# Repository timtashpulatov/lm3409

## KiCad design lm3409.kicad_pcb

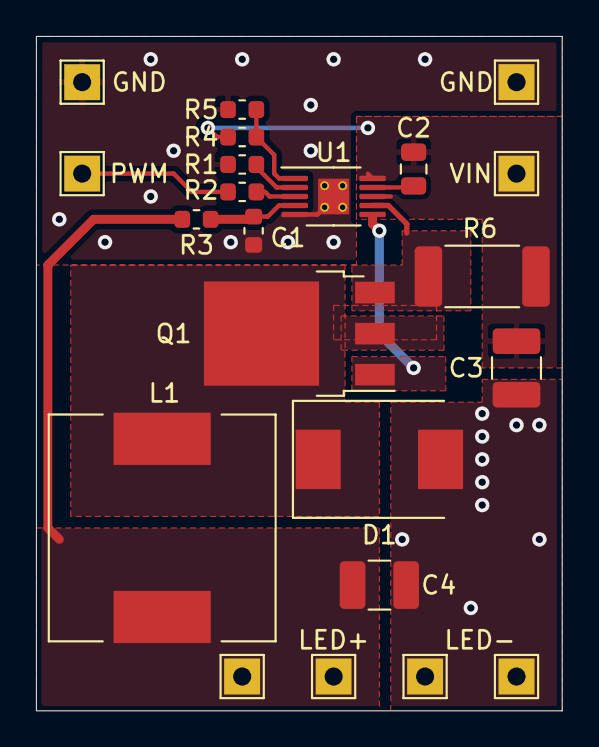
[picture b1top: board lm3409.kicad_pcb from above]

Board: 2 copper layers, 29.2 x 37.5 mm, 22 parts (0 on the bottom side), 12 nets.

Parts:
C1: 470p; C_0603_1608Metric
C2: 1u 50V; C_0805_2012Metric
C3: 10u 50V; C_1210_3225Metric_Pad1.42x2.65mm_HandSolder
C4: TBD; C_1210_3225Metric_Pad1.42x2.65mm_HandSolder
D1: B560C-13-F; D_SMC
GND: GND; TestPoint_THTPad_2.0x2.0mm_Drill1.0mm
GND#2: GND; TestPoint_THTPad_2.0x2.0mm_Drill1.0mm
L1: CDRH127/LDNP-220MC; L_12x12mm_H4.5mm
LED+: +LED; TestPoint_THTPad_2.0x2.0mm_Drill1.0mm
LED+#2: +LED; TestPoint_THTPad_2.0x2.0mm_Drill1.0mm
LED-: LED-; TestPoint_THTPad_2.0x2.0mm_Drill1.0mm
PWM: PWM; TestPoint_THTPad_2.0x2.0mm_Drill1.0mm
Q1: NTD20P06LT4G; TO-252-3_TabPin4
R1: 1K; R_0603_1608Metric
R2: 178K; R_0603_1608Metric
R3: TBD; R_0603_1608Metric
R4: 6K98; R_0603_1608Metric
R5: 49K9; R_0603_1608Metric
R6: WSL2512R2000FEA; R_2512_6332Metric_Pad1.52x3.35mm_HandSolder
TP4: LED-; TestPoint_THTPad_2.0x2.0mm_Drill1.0mm
U1: LM3409HV; MSOP-10-1EP_3x3mm_P0.5mm_EP1.73x1.98mm_ThermalVias
VIN: +VIN; TestPoint_THTPad_2.0x2.0mm_Drill1.0mm

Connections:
/COFF: C1.1, R3.1, U1.4
/CSN: Q1.3, R6.2, U1.7
/IADJ: R2.1, U1.2
/LED+: C4.1, L1.2, LED+.1, LED+#2.1, R3.2
/PGATE: Q1.1, U1.6
/PWM: PWM.1, R1.1
/SW: D1.1, L1.1, Q1.2, Q1.4
/VCC: C2.2, U1.9
/VIN: C2.1, C3.1, R5.1, R6.1, U1.8, U1.10, VIN.1
GND: C1.2, C3.2, C4.2, D1.2, GND.1, GND#2.1, LED-.1, R2.2, R4.2, TP4.1, U1.5, U1.11
unnamed: R1.2, U1.3
unnamed: R4.1, R5.2, U1.1

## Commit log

2021-03-11 Add 3d files
2021-03-12 Update inductor 3d model
2021-03-12 Create fp-info-cache
2021-03-31 Update values
